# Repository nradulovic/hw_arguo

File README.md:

Compact amplifier
=================

This amplifier is intended to be used as a small desktop amplifier. It has no
fancy stuff. It does not even have a volume knob.

It has a short-circuit protection and all the necessary filtering on the inputs
and outputs.

The input is single-ended. 

It has two types of boards:
 - Amplifier board: Mono channel.
 - Power supply board with speaker protection & mute and LED indication.

The complete model of the amplifier case layout is based on Dayens Ampino power 
amplifier.

Amplifier board
===============

Description
-----------

The board contains one amplifier with short-circuit proction and input and
output filters.

Dimensions
----------

Max width: 200mm
Max height: 100mm

Connections
-----------

* Power supply connectors: Vcc, GND, Vee.
* Output connectors: Out, GND.
* Input connector: In, SGND.

Power supply board
==================

Description
-----------

Dimensions
----------

Max width: 140mm
Max height: 100mm

Connections
-----------

* AC Voltage input: Live, Neutral, Earth.
* Switch: CN1, CN2.
* Primary output: Live, Neutral, Earth.
* Secondary input: AC1, GND, AC2.
* DC output: Vcc, GND, Vee.
* Amplifier input: OutL, GND, OutR, GND
* Amplifier output: OutL, GND, OutR, GND
* LED indicator (POWER/FAILURE/OVERLOAD): Anode, Cathode.
* Mute key: K1, K2.

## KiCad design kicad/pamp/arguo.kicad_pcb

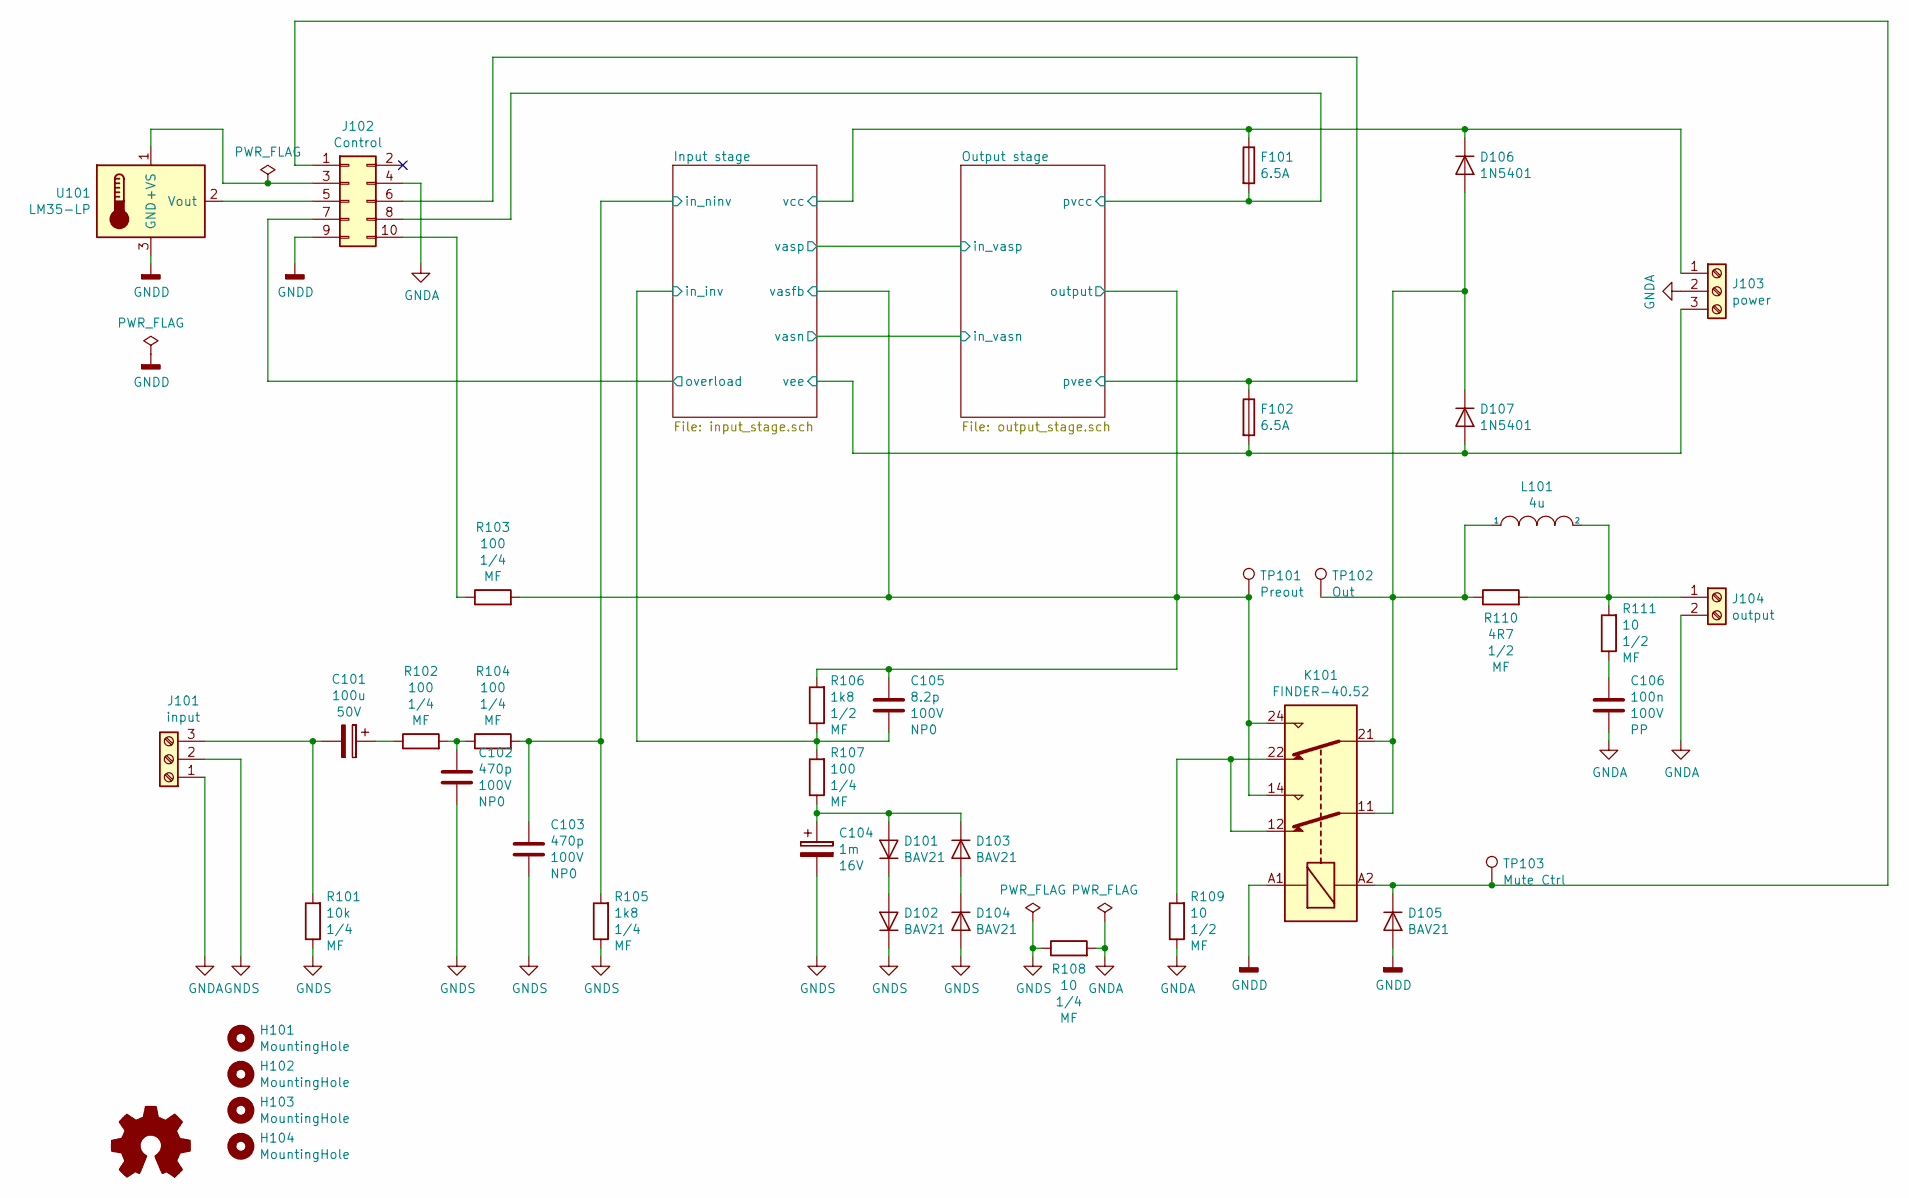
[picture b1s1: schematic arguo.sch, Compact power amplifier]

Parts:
C101: 100u; CP_Radial_D10.0mm_P3.50mm; Voltage 50V
C102, C103: 470p; C_Disc_D8.0mm_W2.5mm_P5.00mm; Voltage 100V
C104: 1m; CP_Radial_D10.0mm_P3.50mm; Voltage 16V
C105: 8.2p; C_Disc_D3.0mm_W2.0mm_P2.50mm; Voltage 100V
C106: 100n; C_Rect_L7.2mm_W5.5mm_P5.00mm_FKS2_FKP2_MKS2_MKP2; Voltage 100V
D101, D102, D103, D104, D105: BAV21; D_DO-41_SOD81_P7.62mm_Horizontal
D106, D107: 1N5401; D_DO-201AD_P15.24mm_Horizontal
F101, F102: 6.5A; Fuseholder_Cylinder-5x20mm_Schurter_0031_8201_Horizontal_Op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
H101, H102, H103, H104: MountingHole; MountingHole_3.2mm_M3_Pad
J101: input; TerminalBlock_Phoenix_PT-1,5-3-3.5-H_1x03_P3.50mm_Horizontal
J102: Control; IDC-Header_2x05_P2.54mm_Vertical
J103: power; PhoenixContact_MCV_1,5_3-G-3.81_1x03_P3.81mm_Vertical
J104: output; PhoenixContact_MCV_1,5_2-G-3.81_1x02_P3.81mm_Vertical
K101: FINDER-40.52; Relay_DPDT_Finder_40.52
L101: 4u; L_Axial_L29.9mm_D14.0mm_P7.62mm_Vertical_Vishay_IHA-105
R101: 10k; R_Axial_DIN0207_L6.3mm_D2.5mm_P10.16mm_Horizontal
R102, R103, R104, R107: 100; R_Axial_DIN0207_L6.3mm_D2.5mm_P10.16mm_Horizontal
R105: 1k8; R_Axial_DIN0207_L6.3mm_D2.5mm_P10.16mm_Horizontal
R106: 1k8; R_Axial_DIN0411_L9.9mm_D3.6mm_P12.70mm_Horizontal
R108: 10; R_Axial_DIN0207_L6.3mm_D2.5mm_P10.16mm_Horizontal
R109, R111: 10; R_Axial_DIN0411_L9.9mm_D3.6mm_P12.70mm_Horizontal
R110: 4R7; R_Axial_DIN0411_L9.9mm_D3.6mm_P12.70mm_Horizontal
TP101: Preout; TestPoint_Bridge_Pitch2.54mm_Drill0.7mm
TP102: Out; TestPoint_Bridge_Pitch2.54mm_Drill0.7mm
TP103: Mute Ctrl; TestPoint_Bridge_Pitch2.54mm_Drill0.7mm
U101: LM35-LP; TO-92L_Inline_Wide

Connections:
/Input stage/in_inv: C105.2, R106.1, R107.2; also elsewhere on the board
/Input stage/in_ninv: C103.2, R104.2, R105.2; also elsewhere on the board
/Input stage/overload: J102.7; also elsewhere on the board
/Input stage/vcc: D106.1 (K), F101.1, J103.1; also elsewhere on the board
/Input stage/vee: D107.2 (A), F102.2, J103.3; also elsewhere on the board
/Output stage/output: C105.1, K101.14, K101.24, R103.2, R106.2, TP101.1; also elsewhere on the board
/Output stage/pvcc: F101.2, J102.8; also elsewhere on the board
/Output stage/pvee: F102.1, J102.6; also elsewhere on the board
GNDA: C106.2, J101.1, J102.4, J103.2, J104.2, R108.2, R109.1; also elsewhere on the board
GNDD: D105.2 (A), J102.9, K101.A1, U101.3 (GND)
GNDS: C102.1, C103.1, C104.2, D102.1 (K), D104.2 (A), J101.2, R101.1, R105.1, R108.1
unnamed: C101.1, R102.1
unnamed: C101.2, J101.3, R101.2
unnamed: C102.2, R102.2, R104.1
unnamed: C104.1, D101.2 (A), D103.1 (K), R107.1
unnamed: C106.1, R111.1
unnamed: D101.1 (K), D102.2 (A)
unnamed: D103.2 (A), D104.1 (K)
unnamed: D105.1 (K), J102.1, K101.A2, TP103.1
unnamed: D106.2 (A), D107.1 (K), K101.11, K101.21, L101.1, R110.1, TP102.1
unnamed: J102.3, U101.1 (+VS)
unnamed: J102.5, U101.2 (Vout)
unnamed: J102.10, R103.1
unnamed: J104.1, L101.2, R110.2, R111.2
unnamed: K101.12, K101.22, R109.2

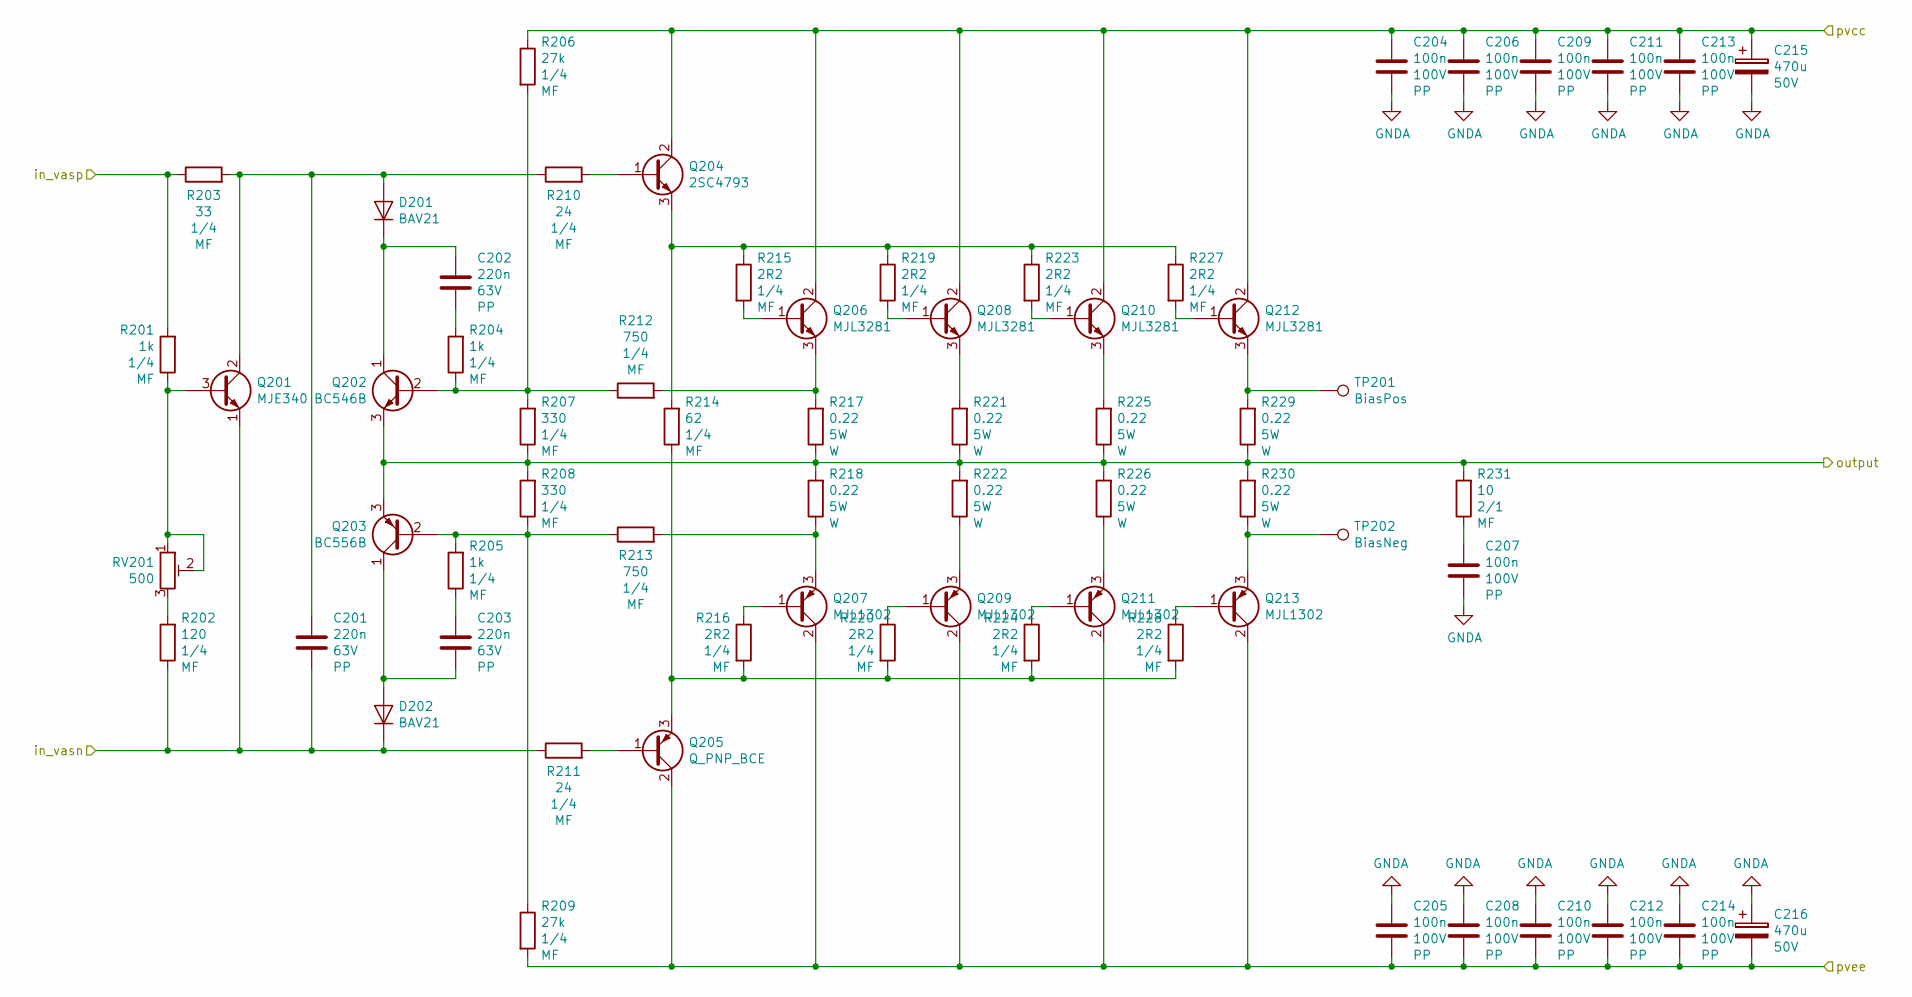
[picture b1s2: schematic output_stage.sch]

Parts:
C201, C202, C203: 220n; C_Rect_L7.2mm_W4.5mm_P5.00mm_FKS2_FKP2_MKS2_MKP2; Voltage 63V
C204, C205, C206, C207, C208, C209, C210, C211, C212, C213, C214: 100n; C_Rect_L7.2mm_W5.5mm_P5.00mm_FKS2_FKP2_MKS2_MKP2; Voltage 100V
C215, C216: 470u; CP_Radial_D17.0mm_P7.50mm; Voltage 50V
D201, D202: BAV21; D_DO-41_SOD81_P7.62mm_Horizontal
Q201: MJE340; TO-126-3_Vertical
Q202: BC546B; TO-92L_Inline_Wide
Q203: BC556B; TO-92L_Inline_Wide
Q204: 2SC4793; TO-220-3_Vertical
Q205: Q_PNP_BCE; TO-220-3_Vertical
Q206, Q208, Q210, Q212: MJL3281; TO-264-3_Vertical
Q207, Q209, Q211, Q213: MJL1302; TO-264-3_Vertical
R201, R204, R205: 1k; R_Axial_DIN0207_L6.3mm_D2.5mm_P10.16mm_Horizontal
R202: 120; R_Axial_DIN0207_L6.3mm_D2.5mm_P10.16mm_Horizontal
R203: 33; R_Axial_DIN0207_L6.3mm_D2.5mm_P10.16mm_Horizontal
R206, R209: 27k; R_Axial_DIN0207_L6.3mm_D2.5mm_P10.16mm_Horizontal
R207, R208: 330; R_Axial_DIN0207_L6.3mm_D2.5mm_P10.16mm_Horizontal
R210, R211: 24; R_Axial_DIN0207_L6.3mm_D2.5mm_P10.16mm_Horizontal
R212, R213: 750; R_Axial_DIN0207_L6.3mm_D2.5mm_P10.16mm_Horizontal
R214: 62; R_Axial_DIN0207_L6.3mm_D2.5mm_P10.16mm_Horizontal
R215, R216, R219, R220, R223, R224, R227, R228: 2R2; R_Axial_DIN0207_L6.3mm_D2.5mm_P10.16mm_Horizontal
R217, R218, R221, R222, R225, R226, R229, R230: 0.22; R_Axial_Power_L20.0mm_W6.4mm_P25.40mm
R231: 10; R_Axial_DIN0411_L9.9mm_D3.6mm_P12.70mm_Horizontal
RV201: 500; Potentiometer_ACP_CA9-V10_Vertical
TP201: BiasPos; TestPoint_Bridge_Pitch2.54mm_Drill0.7mm
TP202: BiasNeg; TestPoint_Bridge_Pitch2.54mm_Drill0.7mm

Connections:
/Output stage/in_vasn: C201.2, D202.1 (K), Q201.1 (E), R202.1, R211.1; also elsewhere on the board
/Output stage/in_vasp: R201.2, R203.1; also elsewhere on the board
/Output stage/output: Q202.3 (E), Q203.3 (E), R207.1, R208.2, R217.1, R218.2, R221.1, R222.2, R225.1, R226.2, R229.1, R230.2, R231.2; also elsewhere on the board
/Output stage/pvcc: C204.1, C206.1, C209.1, C211.1, C213.1, C215.1, Q204.2 (C), Q206.2 (C), Q208.2 (C), Q210.2 (C), Q212.2 (C), R206.1; also elsewhere on the board
/Output stage/pvee: C205.2, C208.2, C210.2, C212.2, C214.2, C216.2, Q205.2 (C), Q207.2 (C), Q209.2 (C), Q211.2 (C), Q213.2 (C), R209.2; also elsewhere on the board
GNDA: C204.2, C205.1, C206.2, C207.2, C208.1, C209.2, C210.1, C211.2, C212.1, C213.2, C214.1, C215.2, C216.1; also elsewhere on the board
unnamed: C201.1, D201.2 (A), Q201.2 (C), R203.2, R210.1
unnamed: C202.1, D201.1 (K), Q202.1 (C)
unnamed: C202.2, R204.2
unnamed: C203.1, R205.1
unnamed: C203.2, D202.2 (A), Q203.1 (C)
unnamed: C207.1, R231.1
unnamed: Q201.3 (B), R201.1, RV201.1, RV201.2
unnamed: Q202.2 (B), R204.1, R206.2, R207.2, R212.1
unnamed: Q203.2 (B), R205.2, R208.1, R209.1, R213.1
unnamed: Q204.1 (B), R210.2
unnamed: Q204.3 (E), R214.2, R215.1, R219.1, R223.1, R227.1
unnamed: Q205.1 (B), R211.2
unnamed: Q205.3 (E), R214.1, R216.2, R220.2, R224.2, R228.2
unnamed: Q206.1 (B), R215.2
unnamed: Q206.3 (E), R212.2, R217.2
unnamed: Q207.1 (B), R216.1
unnamed: Q207.3 (E), R213.2, R218.1
unnamed: Q208.1 (B), R219.2
unnamed: Q208.3 (E), R221.2
unnamed: Q209.1 (B), R220.1
unnamed: Q209.3 (E), R222.1
unnamed: Q210.1 (B), R223.2
unnamed: Q210.3 (E), R225.2
unnamed: Q211.1 (B), R224.1
unnamed: Q211.3 (E), R226.1
unnamed: Q212.1 (B), R227.2
unnamed: Q212.3 (E), R229.2, TP201.1
unnamed: Q213.1 (B), R228.1
unnamed: Q213.3 (E), R230.1, TP202.1
unnamed: R202.2, RV201.3

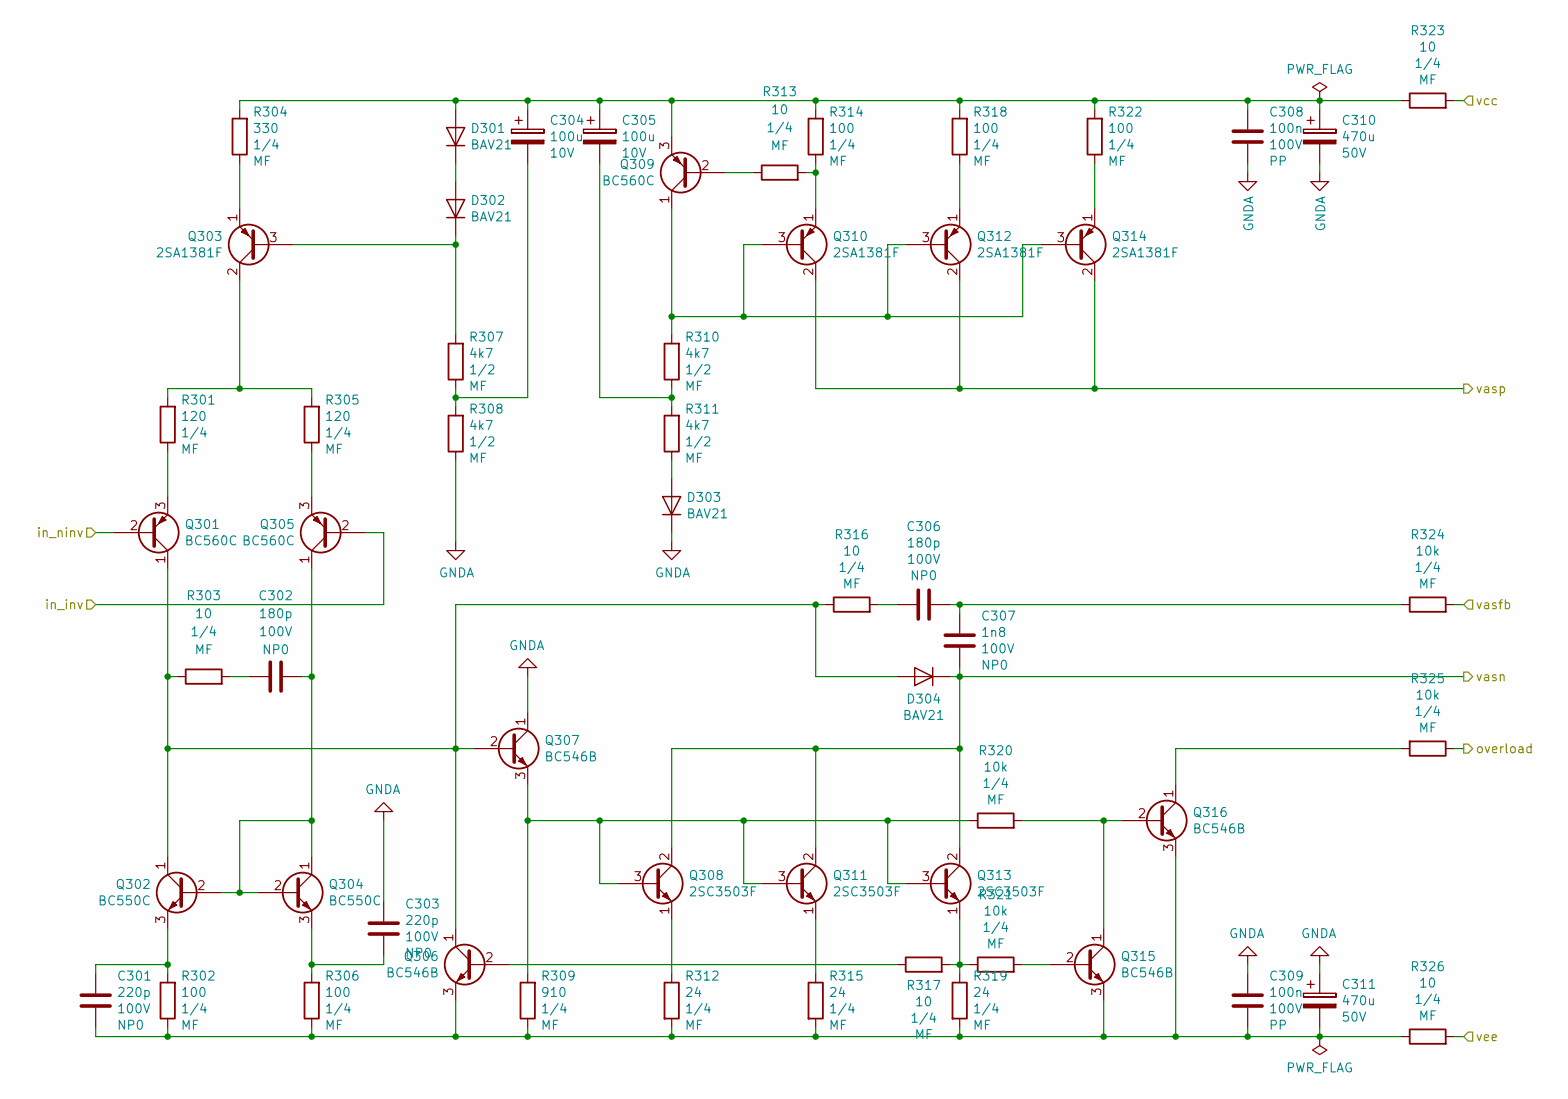
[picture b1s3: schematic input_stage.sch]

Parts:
C301, C303: 220p; C_Disc_D8.0mm_W2.5mm_P5.00mm; Voltage 100V
C302, C306: 180p; C_Disc_D8.0mm_W2.5mm_P5.00mm; Voltage 100V
C304, C305: 100u; CP_Radial_D8.0mm_P2.50mm; Voltage 10V
C307: 1n8; C_Disc_D8.0mm_W2.5mm_P5.00mm; Voltage 100V
C308, C309: 100n; C_Rect_L7.2mm_W5.5mm_P5.00mm_FKS2_FKP2_MKS2_MKP2; Voltage 100V
C310, C311: 470u; CP_Radial_D10.0mm_P3.50mm; Voltage 50V
D301, D302, D303, D304: BAV21; D_DO-41_SOD81_P7.62mm_Horizontal
Q301, Q305, Q309: BC560C; TO-92L_Inline_Wide
Q302, Q304: BC550C; TO-92L_Inline_Wide
Q303: 2SA1381F; TO-126-3_Vertical
Q306, Q307, Q315, Q316: BC546B; TO-92L_Inline_Wide
Q308, Q311, Q313: 2SC3503F; TO-126-3_Horizontal_TabDown
Q310, Q312, Q314: 2SA1381F; TO-126-3_Horizontal_TabDown
R301, R305: 120; R_Axial_DIN0207_L6.3mm_D2.5mm_P10.16mm_Horizontal
R302, R306, R314, R318, R322: 100; R_Axial_DIN0207_L6.3mm_D2.5mm_P10.16mm_Horizontal
R303, R313, R316, R317, R323, R326: 10; R_Axial_DIN0207_L6.3mm_D2.5mm_P10.16mm_Horizontal
R304: 330; R_Axial_DIN0207_L6.3mm_D2.5mm_P10.16mm_Horizontal
R307, R308, R310, R311: 4k7; R_Axial_DIN0411_L9.9mm_D3.6mm_P12.70mm_Horizontal
R309: 910; R_Axial_DIN0207_L6.3mm_D2.5mm_P10.16mm_Horizontal
R312, R315, R319: 24; R_Axial_DIN0207_L6.3mm_D2.5mm_P10.16mm_Horizontal
R320, R321, R324, R325: 10k; R_Axial_DIN0207_L6.3mm_D2.5mm_P10.16mm_Horizontal

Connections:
/Input stage/in_inv: Q305.2 (B); also elsewhere on the board
/Input stage/in_ninv: Q301.2 (B); also elsewhere on the board
/Input stage/overload: R325.1; also elsewhere on the board
/Input stage/vcc: R323.2; also elsewhere on the board
/Input stage/vee: R326.2; also elsewhere on the board
/Output stage/in_vasn: C307.1, D304.1 (K), Q308.2 (C), Q311.2 (C), Q313.2 (C); also elsewhere on the board
/Output stage/in_vasp: Q310.2 (C), Q312.2 (C), Q314.2 (C); also elsewhere on the board
/Output stage/output: R324.2; also elsewhere on the board
GNDA: C303.2, C308.2, C309.1, C310.2, C311.1, D303.1 (K), Q307.1 (C), R308.1; also elsewhere on the board
unnamed: C301.1, C309.2, C311.2, Q306.3 (E), Q315.3 (E), Q316.3 (E), R302.1, R306.1, R309.1, R312.2, R315.2, R319.2, R326.1
unnamed: C301.2, Q302.3 (E), R302.2
unnamed: C302.1, Q302.2 (B), Q304.1 (C), Q304.2 (B), Q305.1 (C)
unnamed: C302.2, R303.2
unnamed: C303.1, Q304.3 (E), R306.2
unnamed: C304.1, C305.1, C308.1, C310.1, D301.2 (A), Q309.3 (E), R304.2, R314.2, R318.2, R322.2, R323.1
unnamed: C304.2, R307.1, R308.2
unnamed: C305.2, R310.1, R311.2
unnamed: C306.1, C307.2, R324.1
unnamed: C306.2, R316.2
unnamed: D301.1 (K), D302.2 (A)
unnamed: D302.1 (K), Q303.3 (B), R307.2
unnamed: D303.2 (A), R311.1
unnamed: D304.2 (A), Q301.1 (C), Q302.1 (C), Q306.1 (C), Q307.2 (B), R303.1, R316.1
unnamed: Q301.3 (E), R301.1
unnamed: Q303.1 (E), R304.1
unnamed: Q303.2 (C), R301.2, R305.2
unnamed: Q305.3 (E), R305.1
unnamed: Q306.2 (B), R317.1
unnamed: Q307.3 (E), Q308.3 (B), Q311.3 (B), Q313.3 (B), R309.2, R320.1
unnamed: Q308.1 (E), R312.1
unnamed: Q309.1 (C), Q310.3 (B), Q312.3 (B), Q314.3 (B), R310.2
unnamed: Q309.2 (B), R313.1
unnamed: Q310.1 (E), R313.2, R314.1
unnamed: Q311.1 (E), R315.1
unnamed: Q312.1 (E), R318.1
unnamed: Q313.1 (E), R317.2, R319.1, R321.1
unnamed: Q314.1 (E), R322.1
unnamed: Q315.1 (C), Q316.2 (B), R320.2
unnamed: Q315.2 (B), R321.2
unnamed: Q316.1 (C), R325.2

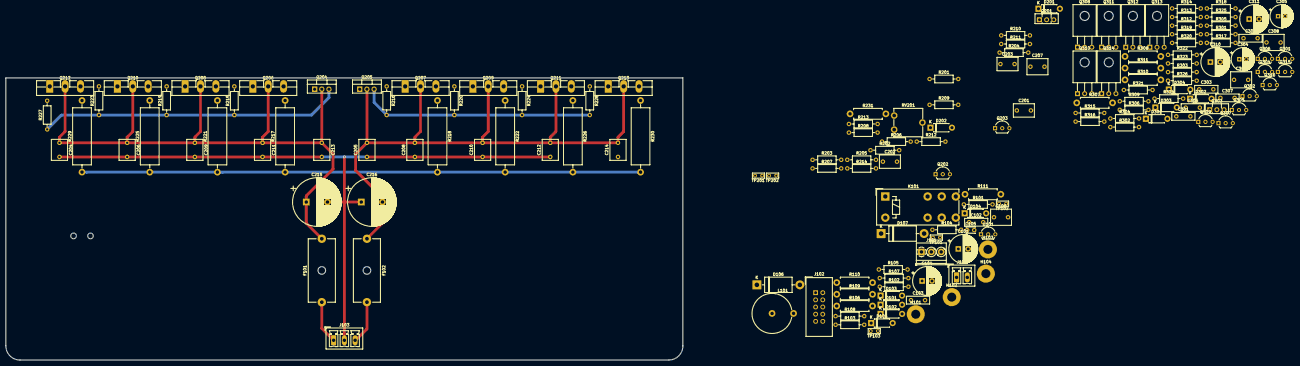
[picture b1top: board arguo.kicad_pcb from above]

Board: 2 copper layers, 240.0 x 100.0 mm, 162 parts (0 on the bottom side), 88 nets.

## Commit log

2019-01-08 Updated gitignore.
2019-02-18 Corrected library paths
2019-02-19 WIP: Class-G Arguo
2019-02-19 Added .fft files to .gitignore
2019-02-24 Using 4 OPS pairs, SR, protection, thermal, thd evaluated.
2019-02-24 Corrected spice paths.
2019-07-30 Solution 1. for high current routing.
2019-08-31 First variant.
2020-04-22 Added protection calculation excel sheet.
2021-08-18 chore: consolidating projects
2021-08-18 chore: updated specifications
